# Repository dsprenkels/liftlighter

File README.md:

# LiftLighter

I once found an old lift indicator in Radboud University's Faculty of
Science (credits to Luuk van Summeren). If you don't know what I mean,
[here is an example][photo].

The indicator has ten lights: down, 1, 2, 3, 4, 5, B, S, K and up. This
repository contains the KiCad files for the circuit board and the software
for the _Atmega8_ microcontroller.

## Components

The board (as you can see in the schematic) is reasonably modular. If you are
going to build your own setup, I recommend doing so with a 3.3V power supply
with LEDs instead of 12V lights.

For a breadboard-proof-of-concept:
- 1x Atmega8 microcontroller
- 11x LED + resistor
- 1x 32.768kHz crystal
- 2x 22 pF capacitors (for use with crystal)
- 1x pull-up resistor (30-80kΩ) for reset
- 1x control button

For a very complete setup, add:
- 1x reset button
- 1x switch or pin header w/ jumper for PD5.
- 12V setup
  * 1x 3.3V voltage regulator
  * 1x 100nF capacitor (for use with voltage regulator)
  * 1x 10μF capacitor (for use with voltage regulator)
  * 10x 12V led light + transistor + resistor (instead of LEDs)
  * 1x fuse <!-- TODO calculate threshold value -->
  * 1x 3.3V backup battery
  * 1x diode (for use with backup battery)
  * 1x diode (for prevention of backflow current)
- Pin headers (whichever amount you are going to need)

## Getting started

> If you are interested in this project, ask me personally about it. Although
  I try to keep my documentation complete and readable, I think it may be
  hard to get your setup correctly. Anyway, here goes:

I use a Raspberri Pi to flash my microcontrollers, for this I use a customized
version of the [`avrdude`] tool which uses `linuxspi` ([more info about
this][Raspberri Pi as an AVR Programmer]). If you have your own methods to
flash your microcontrollers you can just use them. In this README I assume you
will be using my method.

1. Install [`KiCad`] (I used version 4.0.3)
2. Install `gcc-avr`, `avr-libc` and **Kevin Cuzner's** [`avrdude`] tool on
   your Raspberri Pi.
3. `git clone https://github.com/dsprenkels/liftlighter.git`
4. `cd liftlighter`
5. Wire up the microcontroller and all the components on a breadboard
   according to the KiCad `liftlighter.sch` file. I recommend tweaking the
   setup, using LEDs instead of 12V lights (which allows you to ditch all the
   transistors). Parts like the 32.768kHz crystal _are_ important!
6. Connect the Raspberri Pi's GPIO pins to the microcontroller (see below).
7. `make flash`
8. Send me an e-mail, because something did not work as expected.

If all went well, the Atmega8 microcontroller should now be executing the
liftlighter

## Wire connections

All the wiring used during the normal operation of the program can be viewed
in `pcb/liftlighter.sch` using KiCad. Furthermore, a PCB layout can be found
in `pcb/liftlighter.kicad_pcb`.

To flash the microcontroller, I use my Raspberri Pi and Kevin Cuzner's
[`avrdude`] tool. When using this setup, you will have to connect the following
(physically numbered) pins:

| type | Pi  | Atmega8  |
| ---- | --- | -------- |
| Vcc  | 17  |  7 & 2   |
| GND  | 20  |  8 & 22  |
| RST  | 22  |  1 (PC6) |
| MOSI | 19  | 17 (PB3) |
| MISO | 21  | 18 (PB4) |
| SCLK | 23  | 19       |

You can actually use any free GPIO pin for reset, as long as you tell `arvdude`
which one you are using [in the Makefile][reset pin].

`make fuse` calls `avrdude` and the Pi should immediately see the Atmega8. If
it does not work, check your connections. More reading about using a Raspberri
Pi to flash a microcontroller can be found [on Cuzner's blog][Raspberri Pi as
an AVR programmer]. Additionally, you may find the [datasheet for the
Atmega8][atmega8] helpful. You can also write me an email.

## Questions

Feel free to send me an email on my Github associated e-mail address.

[photo]: photo.jpg
[`KiCad`]: http://kicad-pcb.org/
[`avrdude`]: https://github.com/kcuzner/avrdude
[Raspberri Pi as an AVR programmer]: http://kevincuzner.com/2013/05/27/raspberry-pi-as-an-avr-programmer/
[reset pin]: https://github.com/dsprenkels/liftlighter/blob/master/Makefile#L9
[atmega8]: http://www.atmel.com/Images/Atmel-2486-8-bit-AVR-microcontroller-ATmega8_L_datasheet.pdf

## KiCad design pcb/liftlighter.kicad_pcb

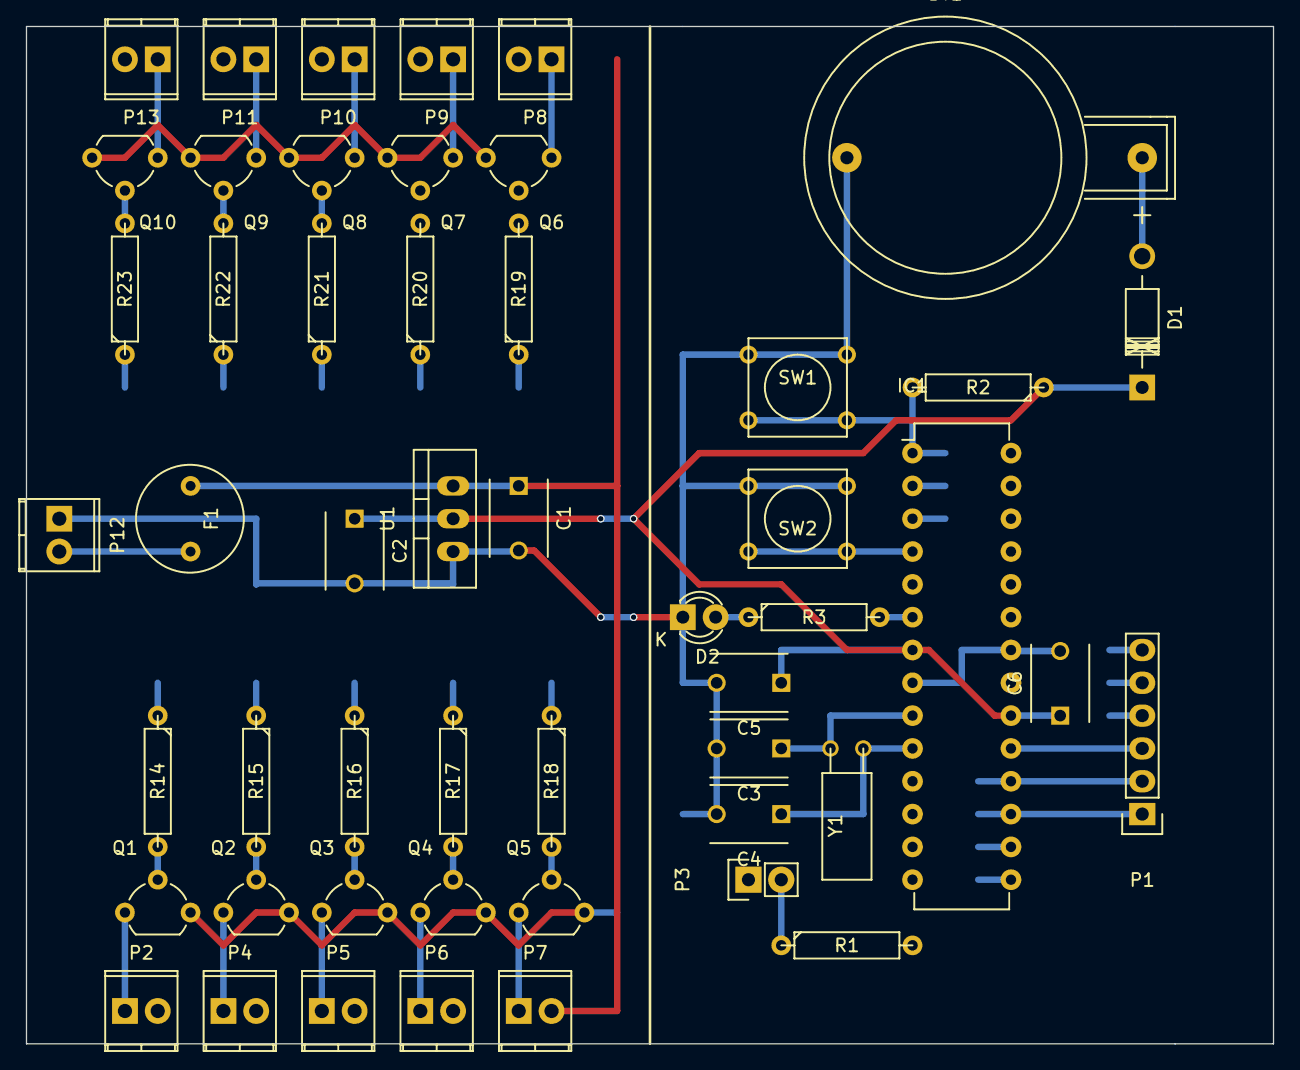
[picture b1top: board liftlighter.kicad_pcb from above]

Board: 2 copper layers, 96.5 x 78.7 mm, 51 parts (0 on the bottom side), 44 nets.

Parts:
BT1: 3V; CR2032H
C1, C5, C6: 100nF; C_Disc_D6_P5
C2: 10uF; C_Disc_D6_P5
C3, C4: 22pF; C_Disc_D6_P5
D1: D; Diode_DO-41_SOD81_Horizontal_RM10
D2: LED; LED-3MM
F1: FUSE; FUSE_ROUND
IC1: ATMEGA8-P; DIP-28_W7.62mm
P1: CONN_01X06; Pin_Header_Straight_1x06
P2, P4, P5, P6, P7, P8, P9, P10, P11, P12, P13: CONN_01X02; TerminalBlock_Pheonix_MPT-2.54mm_2pol
P3: CONN_01X02; Pin_Header_Straight_1x02
Q1, Q2, Q3, Q4, Q5, Q6, Q7, Q8, Q9, Q10: BC548; TO-92_Molded_Wide
R1, R2: 50K; R4
R3: 160; R4
R14, R15, R16, R17, R18, R19, R20, R21, R22, R23: R; R4
SW1, SW2: SW_PUSH; SW_PUSH_SMALL
U1: LD1117S33TR; TO-220_Neutral123_Vertical
Y1: Crystal; Crystal_Watch

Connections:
+12V: C1.1, F1.2, P2.2, P4.2, P5.2, P6.2, P7.2, P8.2, P9.2, P10.2, P11.2, P13.2, U1.3
/a0: IC1.14, R14.1
/a1: IC1.15, R15.1
/a2: IC1.16, R16.1
/a3: IC1.17, P1.1, R17.1
/a4: IC1.18, P1.2, R18.1
/a5: IC1.19, P1.3, R19.1
/a6: IC1.23, R20.1
/a7: IC1.24, R21.1
/a8: IC1.25, R22.1
/a9: IC1.26, R23.1
GND: BT1.2, C1.2, C2.2, C3.2, C4.2, C5.2, C6.2, D2.1, IC1.8, IC1.22, P12.1, Q1.3, Q2.3, Q3.3, Q4.3, Q5.3, Q6.3, Q7.3, Q8.3, Q9.3, Q10.3, R1.2, SW1.1, SW2.2, U1.1
unnamed: BT1.1, D1.2
unnamed: C3.1, IC1.9, Y1.1
unnamed: C4.1, IC1.10, Y1.2
unnamed: D2.2, R3.1
unnamed: F1.1, P12.2
unnamed: IC1.1, P1.6, R2.2, SW1.2
unnamed: IC1.2, P1.5
unnamed: IC1.3, P1.4
unnamed: IC1.4, SW2.1
unnamed: IC1.6, R3.2
unnamed: IC1.11, P3.2, R1.1
unnamed: P2.1, Q1.1
unnamed: P4.1, Q2.1
unnamed: P5.1, Q3.1
unnamed: P6.1, Q4.1
unnamed: P7.1, Q5.1
unnamed: P8.1, Q6.1
unnamed: P9.1, Q7.1
unnamed: P10.1, Q8.1
unnamed: P11.1, Q9.1
unnamed: P13.1, Q10.1
unnamed: Q1.2, R14.2
unnamed: Q2.2, R15.2
unnamed: Q3.2, R16.2
unnamed: Q4.2, R17.2
unnamed: Q5.2, R18.2
unnamed: Q6.2, R19.2
unnamed: Q7.2, R20.2
unnamed: Q8.2, R21.2
unnamed: Q9.2, R22.2
unnamed: Q10.2, R23.2
VCC: C2.1, C5.1, C6.1, D1.1, IC1.7, IC1.20, P3.1, R2.1, U1.2

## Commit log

2016-01-28 fixed bad tickrate
2017-03-17 archive lighter.py
2017-03-22 Add core funtionality
2017-03-22 add KiCad files
2017-03-22 Add time control functionality
2017-03-22 Replace Python .gitingore file with C .gitignore file
2017-03-23 Add a simple README file
2017-03-23 Add MIT license
2017-03-23 Makefile: {.fuzzy => .PHONY}
    Stupid mistake. ".fuzzy" is `.po` files, not Makefiles.
2017-03-23 Makefile: add more compiler warnings
2017-03-23 Be (a lot) stricter about types
    As we are working on a non-conventional platform, we should be
    careful about our integer sizes. For example, a default integer
    size is 16 bits, which is too small to contain our `TICK` global
    variable.
2017-03-23 fix typo
2017-03-23 readme: note that is was at the Radboud University
2017-03-28 Add photo from the thing
2017-04-19 Increase drill hole size for TE connector
2017-04-23 Update twice per second
2017-04-30 Add pull-down resistor for control button
2017-10-07 Remove USART and fix timing bug
2017-10-07 Fix lights order
2017-10-21 Finish main functionality
2017-12-04 Backup time every day
2017-12-05 Add debugging over UART
